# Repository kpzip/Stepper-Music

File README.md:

# Stepper-Music
Music with Stepper Motors!

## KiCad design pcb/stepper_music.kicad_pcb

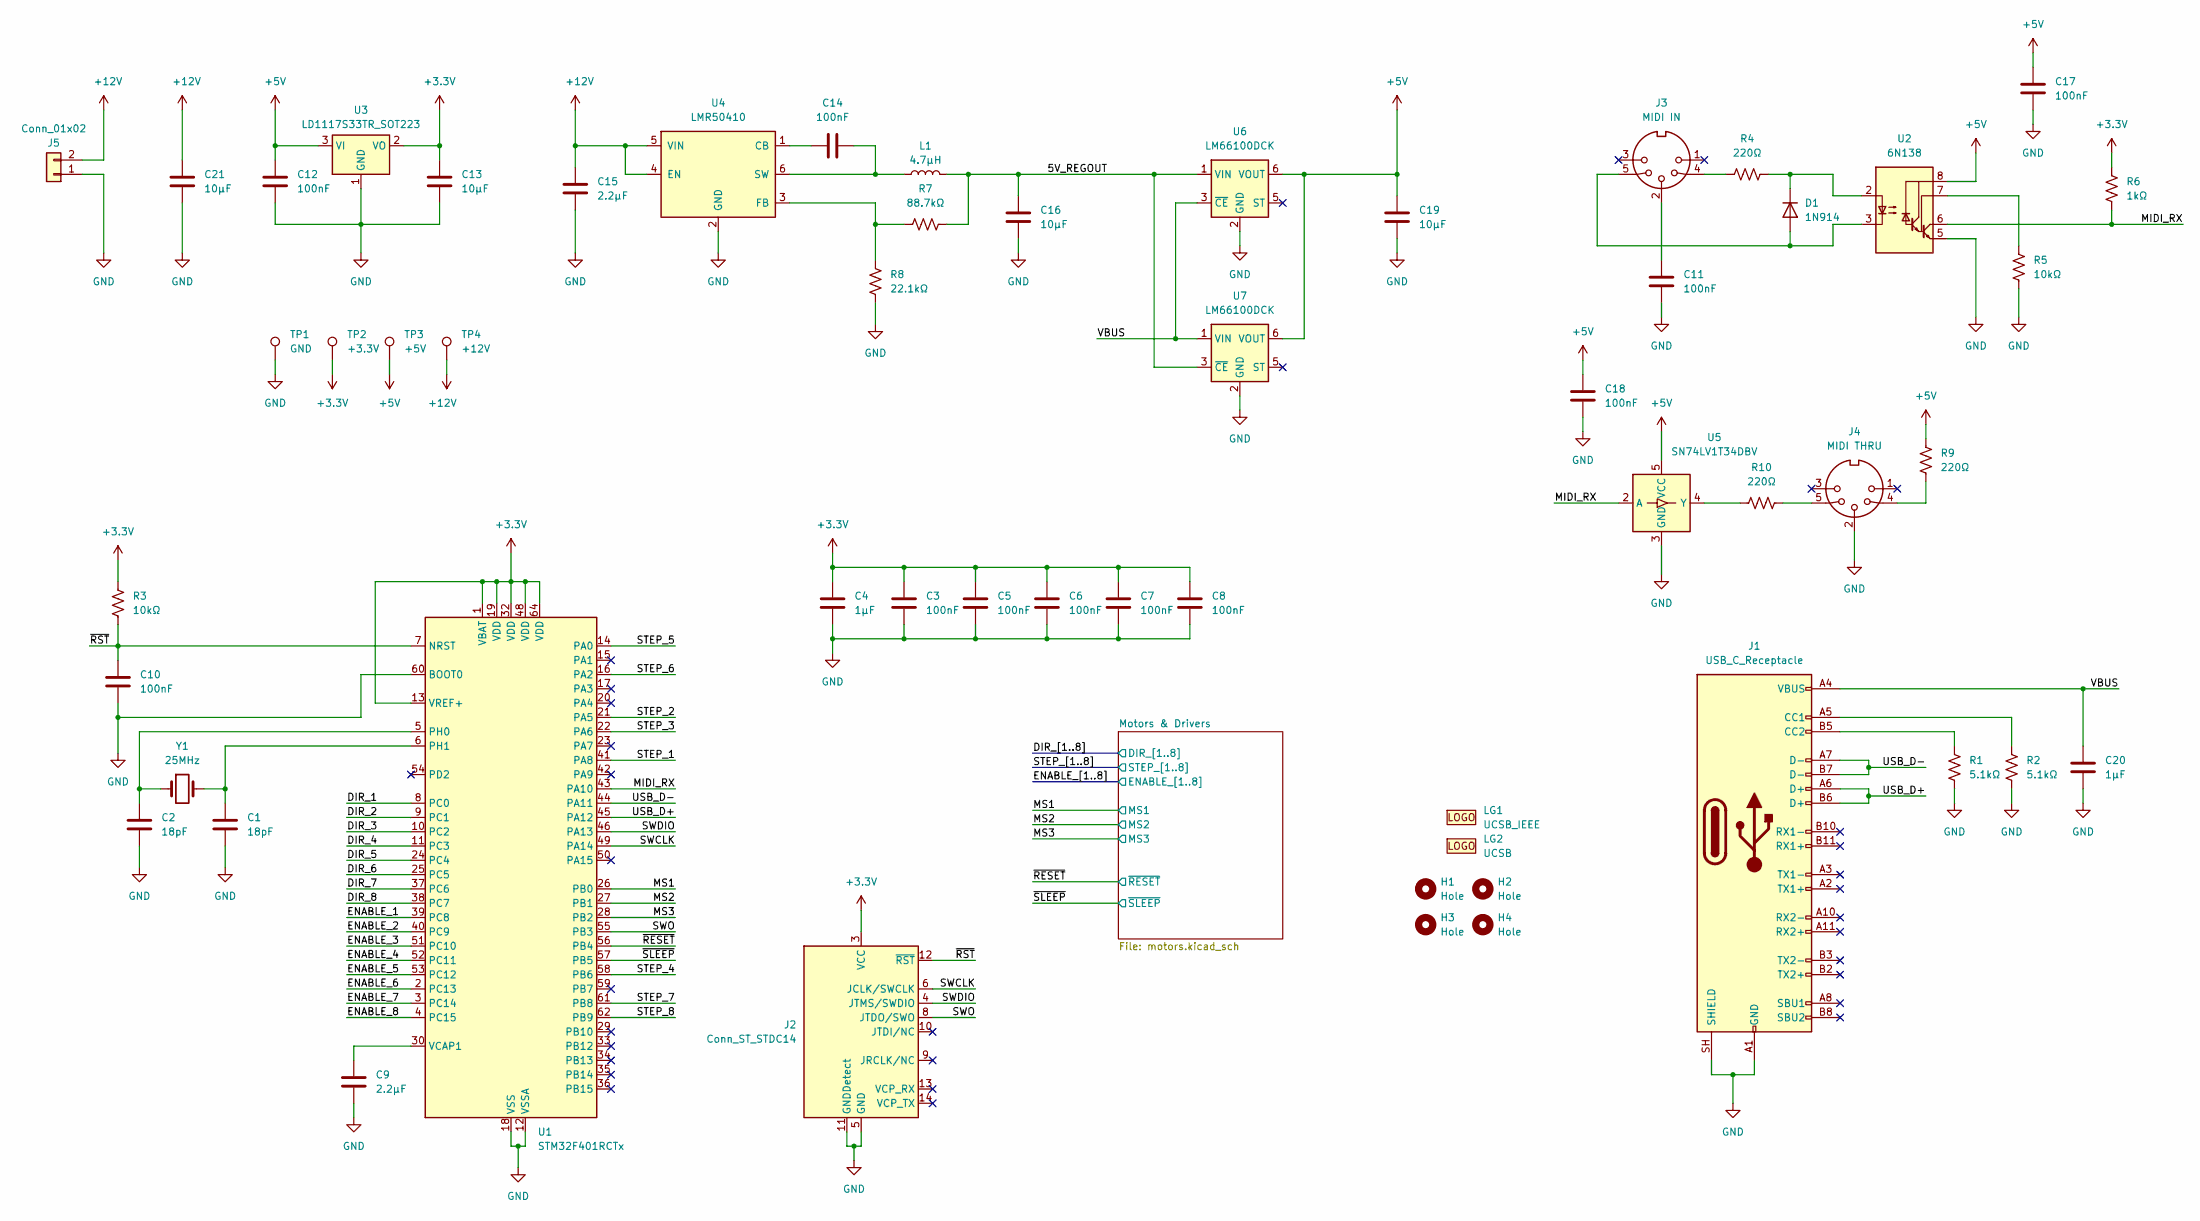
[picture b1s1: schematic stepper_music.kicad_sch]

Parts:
C1, C2: 18pF; C_0402_1005Metric; Manufacturer Part Number GJM1555C1H180GB01D
C3, C5, C6, C7, C8, C10, C11, C12, C14, C17, C18: 100nF; C_1206_3216Metric_Pad1.33x1.80mm_HandSolder; Manufacturer Part Number 1206B104K500CT
C4, C20: 1μF; C_1206_3216Metric_Pad1.33x1.80mm_HandSolder; Manufacturer Part Number CL31B105KAHNNNE
C9, C15: 2.2μF; C_1206_3216Metric_Pad1.33x1.80mm_HandSolder; Manufacturer Part Number UMK316BJ225KD-T
C13, C16, C19, C21: 10μF; C_1206_3216Metric_Pad1.33x1.80mm_HandSolder; Manufacturer Part Number 1276-1181-1-ND
D1: 1N914; D_SOD-523; Manufacturer Part Number 1N914BWT
H1, H2, H3, H4: Hole; MountingHole_3.2mm_M3_DIN965
J1: USB_C_Receptacle; USB_C_Receptacle_short; Manufacturer Part Number USB4056-03-A
J2: Conn_ST_STDC14; PinHeader_2x07_P1.27mm_Vertical_SMD; Manufacturer Part Number FTSH-107-01-L-DV-K
J3: MIDI IN; KYCON_KCDX-5S-N; Manufacturer Part Number KCDX-5S-N
J4: MIDI THRU; KYCON_KCDX-5S-N; Manufacturer Part Number KCDX-5S-N
J5: Conn_01x02; AMASS_XT30PW-M_1x02_P2.50mm_Horizontal; Manufacturer Part Number XT30PW-M30
L1: 4.7μH; L_1008_2520Metric_Pad1.43x2.20mm_HandSolder; Manufacturer Part Number DFE252012P-4R7M=P2
LG1: UCSB_IEEE; UCSB_IEEE_Logo
LG2: UCSB; UCSB_Medium
R1, R2: 5.1kΩ; R_1206_3216Metric_Pad1.30x1.75mm_HandSolder; Manufacturer Part Number RC1206FR-075K1L
R3, R5: 10kΩ; R_1206_3216Metric_Pad1.30x1.75mm_HandSolder; Manufacturer Part Number RMCF1206FT10K0
R4, R9, R10: 220Ω; R_1206_3216Metric_Pad1.30x1.75mm_HandSolder; Manufacturer Part Number RMCF1206FT220R
R6: 1kΩ; R_1206_3216Metric_Pad1.30x1.75mm_HandSolder; Manufacturer Part Number RC1206FR-071KL
R7: 88.7kΩ; R_1206_3216Metric_Pad1.30x1.75mm_HandSolder; Manufacturer Part Number RC1206FR-0788K7L
R8: 22.1kΩ; R_1206_3216Metric_Pad1.30x1.75mm_HandSolder; Manufacturer Part Number CRCW120622K1FKEAC
TP1: GND; TestPoint_Pad_D1.5mm
TP2: +3.3V; TestPoint_Pad_D1.5mm
TP3: +5V; TestPoint_Pad_D1.5mm
TP4: +12V; TestPoint_Pad_D1.5mm
U1: STM32F401RCTx; LQFP-64_10x10mm_P0.5mm; Manufacturer Part Number STM32F401RCT6
U2: 6N138; SOIC-8_3.9x4.9mm_P1.27mm; Manufacturer Part Number HCPL-0701
U3: LD1117S33TR_SOT223; SOT-223-3_TabPin2; Manufacturer Part Number LD1117S33TR
U4: LMR50410; SOT-23-6; Manufacturer Part Number 296-LMR50410Y5FQDBVRQ1CT-ND
U5: SN74LV1T34DBV; SOT-23-5; Manufacturer Part Number SN74LV1T34DBVR
U6, U7: LM66100DCK; SOT-363_SC-70-6; Manufacturer Part Number LM66100DCKR
Y1: 25MHz; Crystal_SMD_HC49-SD; Manufacturer Part Number ECS-250-18-5PX-F-TR

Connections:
+3.3V: C3.1, C4.1, C5.1, C6.1, C7.1, C8.1, C13.1, J2.3 (VCC), R3.1, R6.1, TP2.1 (1_1), U1.1 (VBAT), U1.13 (VREF+), U1.19 (VDD), U1.32 (VDD), U1.48 (VDD), U1.64 (VDD), U3.2 (VO); also elsewhere on the board
+5V: C12.1, C17.1, C18.1, C19.1, R9.2, TP3.1 (1_1), U2.8 (VCC), U3.3 (VI), U5.5 (VCC), U6.6 (VOUT), U7.6 (VOUT)
+12V: C15.1, C21.1, J5.2, TP4.1 (1_1), U4.4 (EN), U4.5 (VIN); also elsewhere on the board
/5V_REGOUT: C16.1, L1.2, R7.2, U6.1 (VIN), U7.3 (~CE)
/DIR_1: U1.8 (PC0); also elsewhere on the board
/DIR_2: U1.9 (PC1); also elsewhere on the board
/DIR_3: U1.10 (PC2); also elsewhere on the board
/DIR_4: U1.11 (PC3); also elsewhere on the board
/DIR_5: U1.24 (PC4); also elsewhere on the board
/DIR_6: U1.25 (PC5); also elsewhere on the board
/DIR_7: U1.37 (PC6); also elsewhere on the board
/DIR_8: U1.38 (PC7); also elsewhere on the board
/ENABLE_1: U1.39 (PC8); also elsewhere on the board
/ENABLE_2: U1.40 (PC9); also elsewhere on the board
/ENABLE_3: U1.51 (PC10); also elsewhere on the board
/ENABLE_4: U1.52 (PC11); also elsewhere on the board
/ENABLE_5: U1.53 (PC12); also elsewhere on the board
/ENABLE_6: U1.2 (PC13); also elsewhere on the board
/ENABLE_7: U1.3 (PC14); also elsewhere on the board
/ENABLE_8: U1.4 (PC15); also elsewhere on the board
/MIDI_RX: R6.2, U1.43 (PA10), U2.6 (VO2), U5.2 (A)
/MS1: U1.26 (PB0); also elsewhere on the board
/MS2: U1.27 (PB1); also elsewhere on the board
/MS3: U1.28 (PB2); also elsewhere on the board
/STEP_1: U1.41 (PA8); also elsewhere on the board
/STEP_2: U1.21 (PA5); also elsewhere on the board
/STEP_3: U1.22 (PA6); also elsewhere on the board
/STEP_4: U1.58 (PB6); also elsewhere on the board
/STEP_5: U1.14 (PA0); also elsewhere on the board
/STEP_6: U1.16 (PA2); also elsewhere on the board
/STEP_7: U1.61 (PB8); also elsewhere on the board
/STEP_8: U1.62 (PB9); also elsewhere on the board
/SWCLK: J2.6 (JCLK/SWCLK), U1.49 (PA14)
/SWDIO: J2.4 (JTMS/SWDIO), U1.46 (PA13)
/SWO: J2.8 (JTDO/SWO), U1.55 (PB3)
/USB_D+: J1.A6 (D+), J1.B6 (D+), U1.45 (PA12)
/USB_D-: J1.A7 (D-), J1.B7 (D-), U1.44 (PA11)
/VBUS: C20.1, J1.A4 (VBUS), J1.A9 (VBUS), J1.B4 (VBUS), J1.B9 (VBUS), U6.3 (~CE), U7.1 (VIN)
/~RESET: U1.56 (PB4); also elsewhere on the board
/~RST: C10.1, J2.12 (~RST), R3.2, U1.7 (NRST)
/~SLEEP: U1.57 (PB5); also elsewhere on the board
GND: C1.2, C2.2, C3.2, C4.2, C5.2, C6.2, C7.2, C8.2, C9.2, C10.2, C11.2, C12.2, C13.2, C15.2, C16.2, C17.2, C18.2, C19.2, C20.2, C21.2, J1.A1 (GND), J1.A12 (GND), J1.B1 (GND), J1.B12 (GND), J1.SH (SHIELD), J2.5 (GND), J2.7 (GND), J2.11 (GNDDetect), J4.2, J5.1, R1.2, R2.2, R5.2, R8.2, TP1.1 (1_1), U1.12 (VSSA), U1.18 (VSS), U1.31 (VSS), U1.47 (VSS), U1.60 (BOOT0), U1.63 (VSS), U2.5 (GND), U3.1 (GND), U4.2 (GND), U5.3 (GND), U6.2 (GND), U7.2 (GND); also elsewhere on the board
unnamed: C11.1, J3.2
unnamed: D1.2 (A), J3.5, U2.3 (C2)
unnamed: D1.1 (K), R4.2, U2.2 (C1)
unnamed: J1.A5 (CC1), R2.1
unnamed: J1.B5 (CC2), R1.1
unnamed: J3.4, R4.1
unnamed: J4.4, R9.1
unnamed: J4.5, R10.1
unnamed: C2.1, U1.5 (PH0), Y1.1
unnamed: C1.1, U1.6 (PH1), Y1.2
unnamed: C9.1, U1.30 (VCAP1)
unnamed: R5.1, U2.7 (VO1)
unnamed: C14.1, U4.1 (CB)
unnamed: R7.1, R8.1, U4.3 (FB)
unnamed: C14.2, L1.1, U4.6 (SW)
unnamed: R10.2, U5.4 (Y)

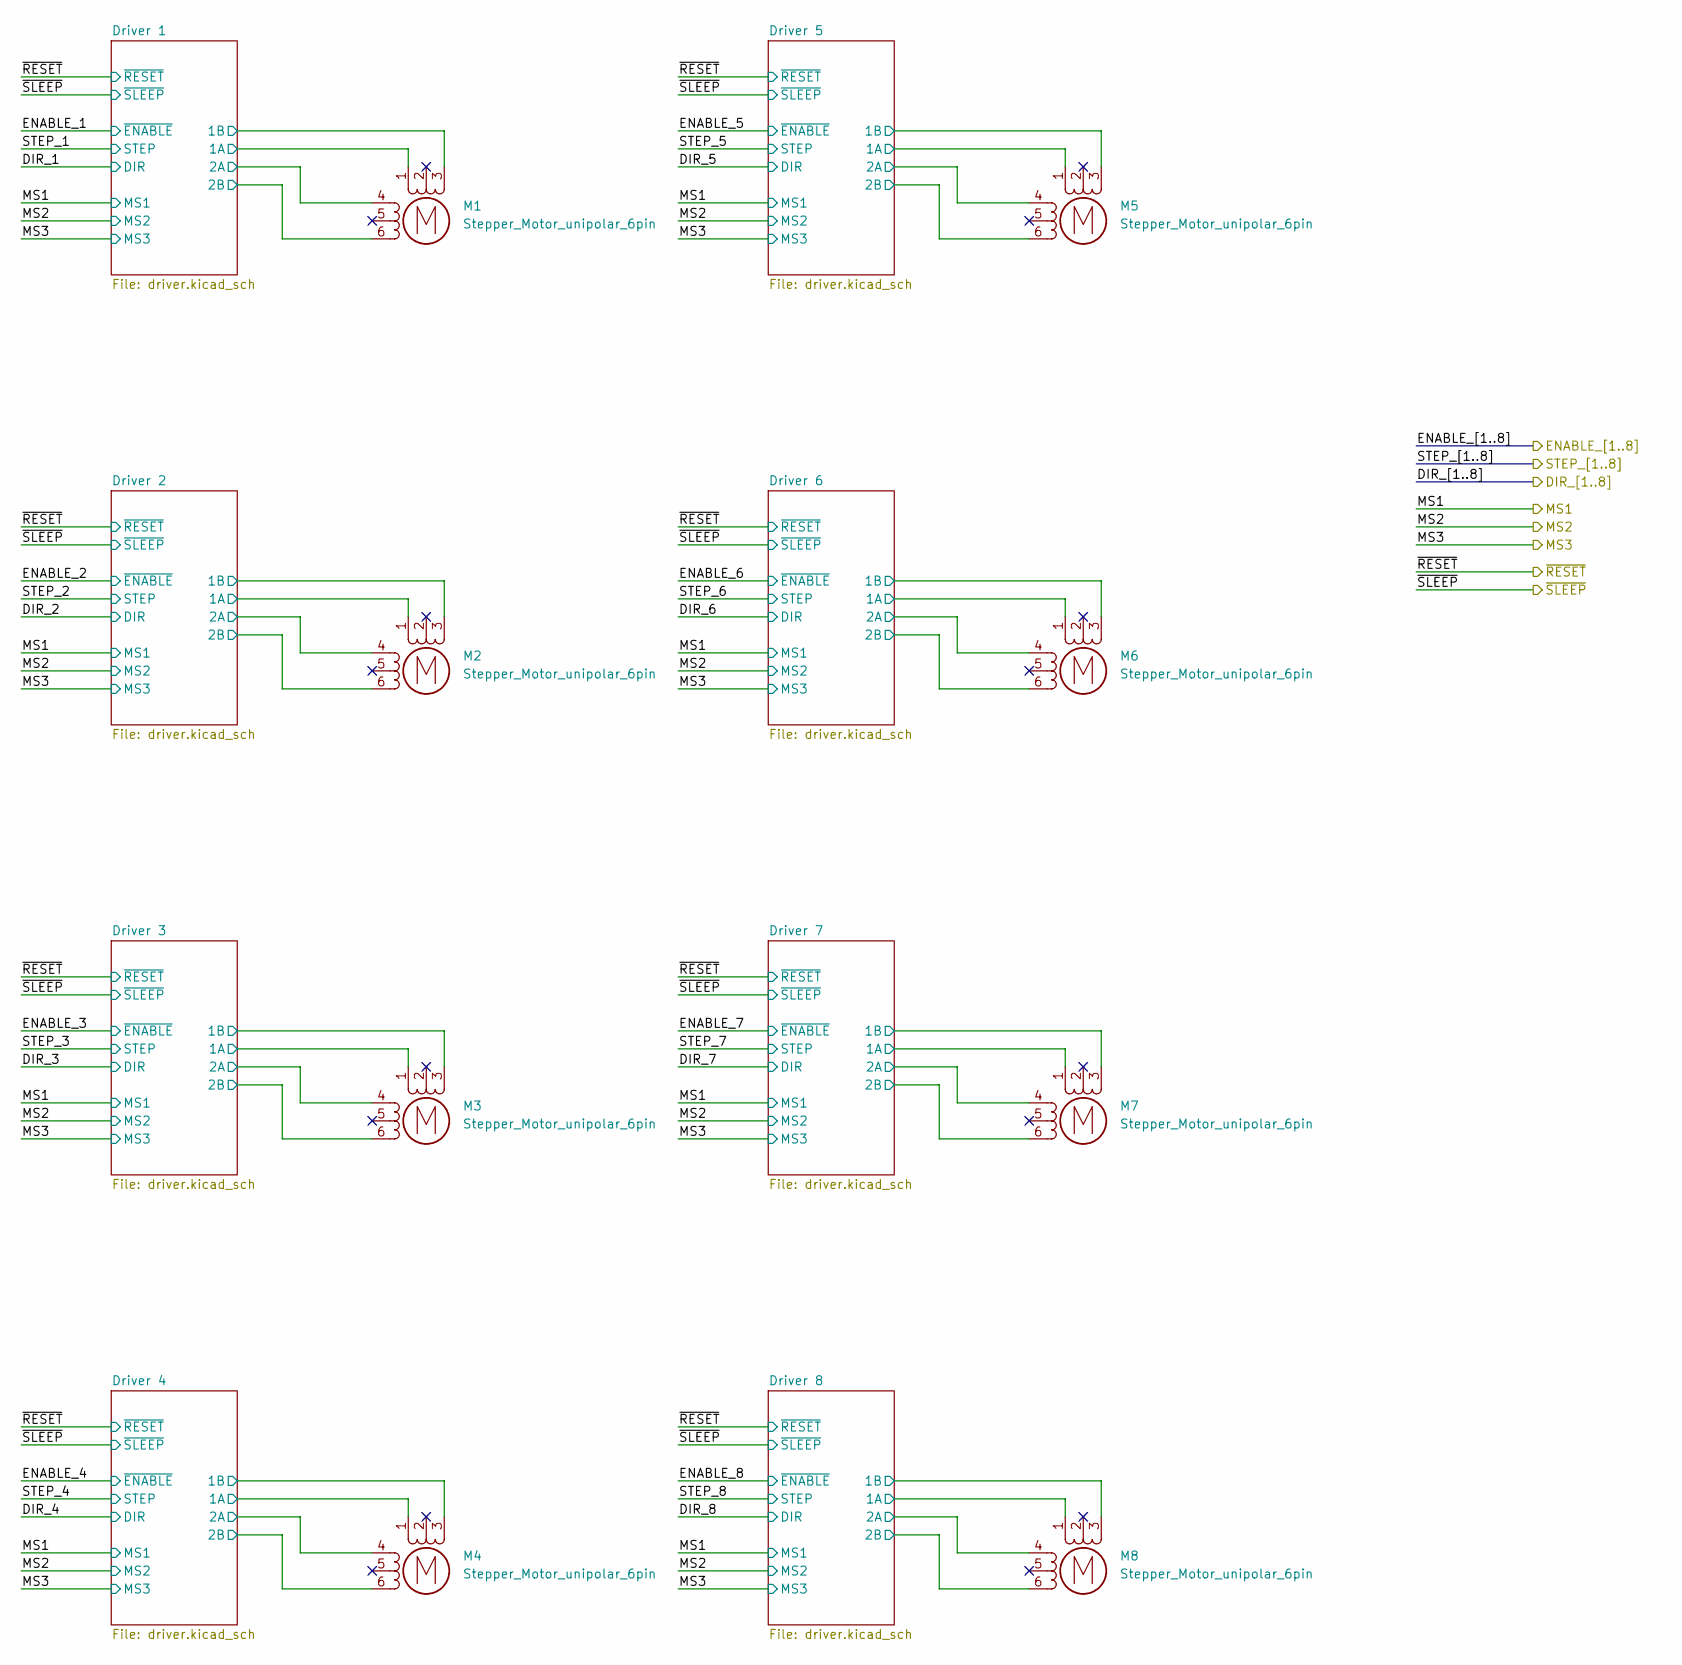
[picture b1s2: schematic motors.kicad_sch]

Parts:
M1, M2, M3, M4, M5, M6, M7, M8: Stepper_Motor_unipolar_6pin; JST_PH_B6B-PH-K_1x06_P2.00mm_Vertical; Manufacturer Part Number B6B-PH-K-S

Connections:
/Motors & Drivers/Driver 1/1A: M1.1; also elsewhere on the board
/Motors & Drivers/Driver 1/1B: M1.3 (-_3); also elsewhere on the board
/Motors & Drivers/Driver 1/2A: M1.4; also elsewhere on the board
/Motors & Drivers/Driver 1/2B: M1.6; also elsewhere on the board
/Motors & Drivers/Driver 2/1A: M2.1; also elsewhere on the board
/Motors & Drivers/Driver 2/1B: M2.3 (-_3); also elsewhere on the board
/Motors & Drivers/Driver 2/2A: M2.4; also elsewhere on the board
/Motors & Drivers/Driver 2/2B: M2.6; also elsewhere on the board
/Motors & Drivers/Driver 3/1A: M3.1; also elsewhere on the board
/Motors & Drivers/Driver 3/1B: M3.3 (-_3); also elsewhere on the board
/Motors & Drivers/Driver 3/2A: M3.4; also elsewhere on the board
/Motors & Drivers/Driver 3/2B: M3.6; also elsewhere on the board
/Motors & Drivers/Driver 4/1A: M4.1; also elsewhere on the board
/Motors & Drivers/Driver 4/1B: M4.3 (-_3); also elsewhere on the board
/Motors & Drivers/Driver 4/2A: M4.4; also elsewhere on the board
/Motors & Drivers/Driver 4/2B: M4.6; also elsewhere on the board
/Motors & Drivers/Driver 5/1A: M5.1; also elsewhere on the board
/Motors & Drivers/Driver 5/1B: M5.3 (-_3); also elsewhere on the board
/Motors & Drivers/Driver 5/2A: M5.4; also elsewhere on the board
/Motors & Drivers/Driver 5/2B: M5.6; also elsewhere on the board
/Motors & Drivers/Driver 6/1A: M6.1; also elsewhere on the board
/Motors & Drivers/Driver 6/1B: M6.3 (-_3); also elsewhere on the board
/Motors & Drivers/Driver 6/2A: M6.4; also elsewhere on the board
/Motors & Drivers/Driver 6/2B: M6.6; also elsewhere on the board
/Motors & Drivers/Driver 7/1A: M7.1; also elsewhere on the board
/Motors & Drivers/Driver 7/1B: M7.3 (-_3); also elsewhere on the board
/Motors & Drivers/Driver 7/2A: M7.4; also elsewhere on the board
/Motors & Drivers/Driver 7/2B: M7.6; also elsewhere on the board
/Motors & Drivers/Driver 8/1A: M8.1; also elsewhere on the board
/Motors & Drivers/Driver 8/1B: M8.3 (-_3); also elsewhere on the board
/Motors & Drivers/Driver 8/2A: M8.4; also elsewhere on the board
/Motors & Drivers/Driver 8/2B: M8.6; also elsewhere on the board

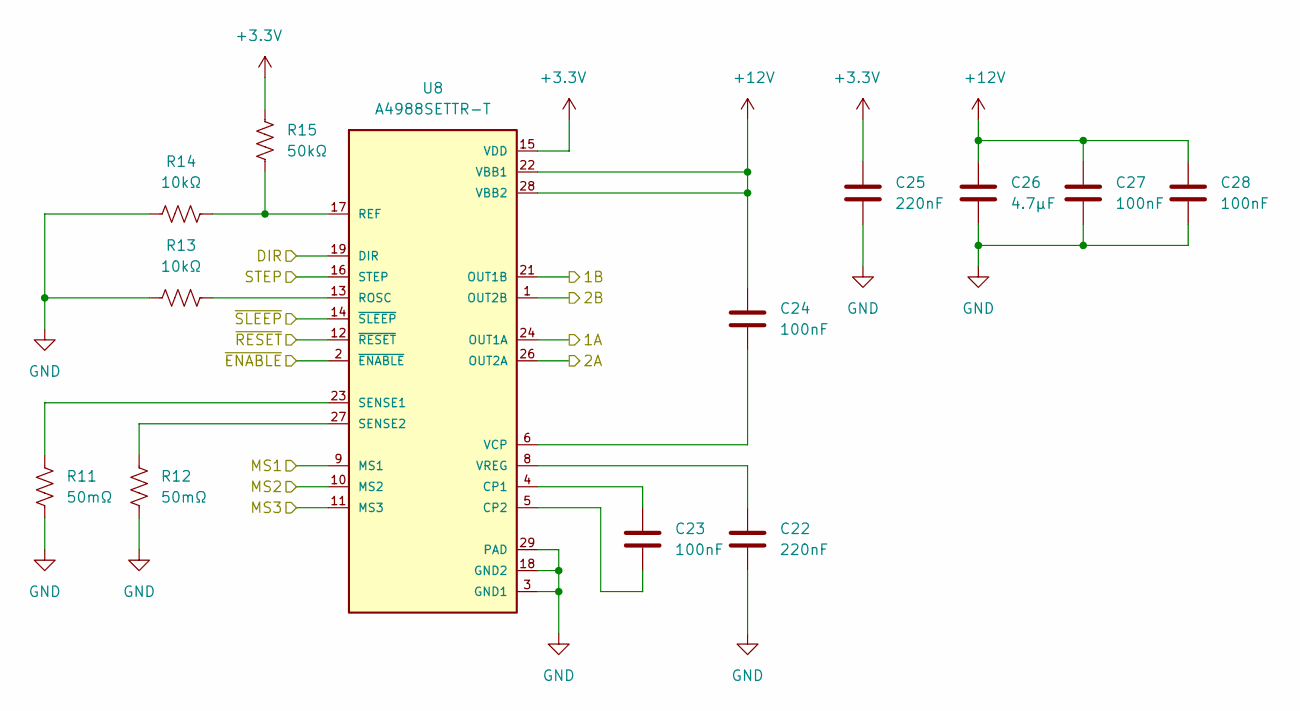
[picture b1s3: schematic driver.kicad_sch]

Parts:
C22, C25: 220nF; C_1206_3216Metric_Pad1.33x1.80mm_HandSolder; Manufacturer Part Number C1206C224K5RACTU
C23, C24, C27, C28: 100nF; C_1206_3216Metric_Pad1.33x1.80mm_HandSolder; Manufacturer Part Number 1206B104K500CT
C26: 4.7μF; C_1206_3216Metric_Pad1.33x1.80mm_HandSolder; Manufacturer Part Number CL31B475KAHNNNE
R11, R12: 50mΩ; R_1206_3216Metric_Pad1.30x1.75mm_HandSolder; Manufacturer Part Number CSR1206FT50L0
R13, R14: 10kΩ; R_1206_3216Metric_Pad1.30x1.75mm_HandSolder; Manufacturer Part Number RMCF1206FT10K0
R15: 50kΩ; R_1206_3216Metric_Pad1.30x1.75mm_HandSolder; Manufacturer Part Number RT1206BRD0750KL
U8: A4988SETTR-T; VQFN-28-1EP_5x5mm_P0.5mm_EP3.25x3.25mm_ThermalVias; Manufacturer Part Number A4988SETTR-T

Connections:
+3.3V: C25.1, R15.2, U8.15 (VDD); also elsewhere on the board
+12V: C24.1, C26.1, C27.1, C28.1, U8.22 (VBB1), U8.28 (VBB2); also elsewhere on the board
/DIR_1: U8.19 (DIR); also elsewhere on the board
/ENABLE_1: U8.2 (~ENABLE); also elsewhere on the board
/MS1: U8.9 (MS1); also elsewhere on the board
/MS2: U8.10 (MS2); also elsewhere on the board
/MS3: U8.11 (MS3); also elsewhere on the board
/Motors & Drivers/Driver 1/1A: U8.24 (OUT1A); also elsewhere on the board
/Motors & Drivers/Driver 1/1B: U8.21 (OUT1B); also elsewhere on the board
/Motors & Drivers/Driver 1/2A: U8.26 (OUT2A); also elsewhere on the board
/Motors & Drivers/Driver 1/2B: U8.1 (OUT2B); also elsewhere on the board
/STEP_1: U8.16 (STEP); also elsewhere on the board
/~RESET: U8.12 (~RESET); also elsewhere on the board
/~SLEEP: U8.14 (~SLEEP); also elsewhere on the board
GND: C22.2, C25.2, C26.2, C27.2, C28.2, R11.2, R12.2, R13.1, R14.1, U8.3 (GND1), U8.18 (GND2), U8.29 (PAD); also elsewhere on the board
unnamed: C23.1, U8.4 (CP1)
unnamed: C23.2, U8.5 (CP2)
unnamed: R14.2, R15.1, U8.17 (REF)
unnamed: R13.2, U8.13 (ROSC)
unnamed: R11.1, U8.23 (SENSE1)
unnamed: R12.1, U8.27 (SENSE2)
unnamed: C24.2, U8.6 (VCP)
unnamed: C22.1, U8.8 (VREG)

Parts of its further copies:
C29, C30, C34, C35, C36, C37, C41, C42, C43, C44, C48, C49, C50, C51, C55, C56, C57, C58, C62, C63, C64, C65, C69, C70, C71, C72, C76, C77: 100nF; C_1206_3216Metric_Pad1.33x1.80mm_HandSolder; Manufacturer Part Number 1206B104K500CT
C31, C32, C38, C39, C45, C46, C52, C53, C59, C60, C66, C67, C73, C74: 220nF; C_1206_3216Metric_Pad1.33x1.80mm_HandSolder; Manufacturer Part Number C1206C224K5RACTU
C33, C40, C47, C54, C61, C68, C75: 4.7μF; C_1206_3216Metric_Pad1.33x1.80mm_HandSolder; Manufacturer Part Number CL31B475KAHNNNE
R16, R17, R21, R22, R26, R27, R31, R32, R36, R37, R41, R42, R46, R47: 50mΩ; R_1206_3216Metric_Pad1.30x1.75mm_HandSolder; Manufacturer Part Number CSR1206FT50L0
R18, R19, R23, R24, R28, R29, R33, R34, R38, R39, R43, R44, R48, R49: 10kΩ; R_1206_3216Metric_Pad1.30x1.75mm_HandSolder; Manufacturer Part Number RMCF1206FT10K0
R20, R25, R30, R35, R40, R45, R50: 50kΩ; R_1206_3216Metric_Pad1.30x1.75mm_HandSolder; Manufacturer Part Number RT1206BRD0750KL
U9, U10, U11, U12, U13, U14, U15: A4988SETTR-T; VQFN-28-1EP_5x5mm_P0.5mm_EP3.25x3.25mm_ThermalVias; Manufacturer Part Number A4988SETTR-T

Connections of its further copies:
+3.3V: C32.1, C39.1, C46.1, C53.1, C60.1, C67.1, C74.1, R20.2, R25.2, R30.2, R35.2, R40.2, R45.2, R50.2, U9.15 (VDD), U10.15 (VDD), U11.15 (VDD), U12.15 (VDD), U13.15 (VDD), U14.15 (VDD), U15.15 (VDD); also elsewhere on the board
+12V: C30.1, C33.1, C34.1, C35.1, C37.1, C40.1, C41.1, C42.1, C44.1, C47.1, C48.1, C49.1, C51.1, C54.1, C55.1, C56.1, C58.1, C61.1, C62.1, C63.1, C65.1, C68.1, C69.1, C70.1, C72.1, C75.1, C76.1, C77.1, U9.22 (VBB1), U9.28 (VBB2), U10.22 (VBB1), U10.28 (VBB2), U11.22 (VBB1), U11.28 (VBB2), U12.22 (VBB1), U12.28 (VBB2), U13.22 (VBB1), U13.28 (VBB2), U14.22 (VBB1), U14.28 (VBB2), U15.22 (VBB1), U15.28 (VBB2); also elsewhere on the board
/DIR_2: U9.19 (DIR); also elsewhere on the board
/DIR_3: U10.19 (DIR); also elsewhere on the board
/DIR_4: U11.19 (DIR); also elsewhere on the board
/DIR_5: U12.19 (DIR); also elsewhere on the board
/DIR_6: U13.19 (DIR); also elsewhere on the board
/DIR_7: U14.19 (DIR); also elsewhere on the board
/DIR_8: U15.19 (DIR); also elsewhere on the board
/ENABLE_2: U9.2 (~ENABLE); also elsewhere on the board
/ENABLE_3: U10.2 (~ENABLE); also elsewhere on the board
/ENABLE_4: U11.2 (~ENABLE); also elsewhere on the board
/ENABLE_5: U12.2 (~ENABLE); also elsewhere on the board
/ENABLE_6: U13.2 (~ENABLE); also elsewhere on the board
/ENABLE_7: U14.2 (~ENABLE); also elsewhere on the board
/ENABLE_8: U15.2 (~ENABLE); also elsewhere on the board
/MS1: U9.9 (MS1), U10.9 (MS1), U11.9 (MS1), U12.9 (MS1), U13.9 (MS1), U14.9 (MS1), U15.9 (MS1); also elsewhere on the board
/MS2: U9.10 (MS2), U10.10 (MS2), U11.10 (MS2), U12.10 (MS2), U13.10 (MS2), U14.10 (MS2), U15.10 (MS2); also elsewhere on the board
/MS3: U9.11 (MS3), U10.11 (MS3), U11.11 (MS3), U12.11 (MS3), U13.11 (MS3), U14.11 (MS3), U15.11 (MS3); also elsewhere on the board
/Motors & Drivers/Driver 2/1A: U9.24 (OUT1A); also elsewhere on the board
/Motors & Drivers/Driver 2/1B: U9.21 (OUT1B); also elsewhere on the board
/Motors & Drivers/Driver 2/2A: U9.26 (OUT2A); also elsewhere on the board
/Motors & Drivers/Driver 2/2B: U9.1 (OUT2B); also elsewhere on the board
/Motors & Drivers/Driver 3/1A: U10.24 (OUT1A); also elsewhere on the board
/Motors & Drivers/Driver 3/1B: U10.21 (OUT1B); also elsewhere on the board
/Motors & Drivers/Driver 3/2A: U10.26 (OUT2A); also elsewhere on the board
/Motors & Drivers/Driver 3/2B: U10.1 (OUT2B); also elsewhere on the board
/Motors & Drivers/Driver 4/1A: U11.24 (OUT1A); also elsewhere on the board
/Motors & Drivers/Driver 4/1B: U11.21 (OUT1B); also elsewhere on the board
/Motors & Drivers/Driver 4/2A: U11.26 (OUT2A); also elsewhere on the board
/Motors & Drivers/Driver 4/2B: U11.1 (OUT2B); also elsewhere on the board
/Motors & Drivers/Driver 5/1A: U12.24 (OUT1A); also elsewhere on the board
/Motors & Drivers/Driver 5/1B: U12.21 (OUT1B); also elsewhere on the board
/Motors & Drivers/Driver 5/2A: U12.26 (OUT2A); also elsewhere on the board
/Motors & Drivers/Driver 5/2B: U12.1 (OUT2B); also elsewhere on the board
/Motors & Drivers/Driver 6/1A: U13.24 (OUT1A); also elsewhere on the board
/Motors & Drivers/Driver 6/1B: U13.21 (OUT1B); also elsewhere on the board
/Motors & Drivers/Driver 6/2A: U13.26 (OUT2A); also elsewhere on the board
/Motors & Drivers/Driver 6/2B: U13.1 (OUT2B); also elsewhere on the board
/Motors & Drivers/Driver 7/1A: U14.24 (OUT1A); also elsewhere on the board
/Motors & Drivers/Driver 7/1B: U14.21 (OUT1B); also elsewhere on the board
/Motors & Drivers/Driver 7/2A: U14.26 (OUT2A); also elsewhere on the board
/Motors & Drivers/Driver 7/2B: U14.1 (OUT2B); also elsewhere on the board
/Motors & Drivers/Driver 8/1A: U15.24 (OUT1A); also elsewhere on the board
/Motors & Drivers/Driver 8/1B: U15.21 (OUT1B); also elsewhere on the board
/Motors & Drivers/Driver 8/2A: U15.26 (OUT2A); also elsewhere on the board
/Motors & Drivers/Driver 8/2B: U15.1 (OUT2B); also elsewhere on the board
/STEP_2: U9.16 (STEP); also elsewhere on the board
/STEP_3: U10.16 (STEP); also elsewhere on the board
/STEP_4: U11.16 (STEP); also elsewhere on the board
/STEP_5: U12.16 (STEP); also elsewhere on the board
/STEP_6: U13.16 (STEP); also elsewhere on the board
/STEP_7: U14.16 (STEP); also elsewhere on the board
/STEP_8: U15.16 (STEP); also elsewhere on the board
/~RESET: U9.12 (~RESET), U10.12 (~RESET), U11.12 (~RESET), U12.12 (~RESET), U13.12 (~RESET), U14.12 (~RESET), U15.12 (~RESET); also elsewhere on the board
/~SLEEP: U9.14 (~SLEEP), U10.14 (~SLEEP), U11.14 (~SLEEP), U12.14 (~SLEEP), U13.14 (~SLEEP), U14.14 (~SLEEP), U15.14 (~SLEEP); also elsewhere on the board
GND: C31.2, C32.2, C33.2, C34.2, C35.2, C38.2, C39.2, C40.2, C41.2, C42.2, C45.2, C46.2, C47.2, C48.2, C49.2, C52.2, C53.2, C54.2, C55.2, C56.2, C59.2, C60.2, C61.2, C62.2, C63.2, C66.2, C67.2, C68.2, C69.2, C70.2, C73.2, C74.2, C75.2, C76.2, C77.2, R16.2, R17.2, R18.1, R19.1, R21.2, R22.2, R23.1, R24.1, R26.2, R27.2, R28.1, R29.1, R31.2, R32.2, R33.1, R34.1, R36.2, R37.2, R38.1, R39.1, R41.2, R42.2, R43.1, R44.1, R46.2, R47.2, R48.1, R49.1, U9.3 (GND1), U9.18 (GND2), U9.29 (PAD), U10.3 (GND1), U10.18 (GND2), U10.29 (PAD), U11.3 (GND1), U11.18 (GND2), U11.29 (PAD), U12.3 (GND1), U12.18 (GND2), U12.29 (PAD), U13.3 (GND1), U13.18 (GND2), U13.29 (PAD), U14.3 (GND1), U14.18 (GND2), U14.29 (PAD), U15.3 (GND1), U15.18 (GND2), U15.29 (PAD); also elsewhere on the board
unnamed: C29.1, U9.4 (CP1)
unnamed: C29.2, U9.5 (CP2)
unnamed: R18.2, R20.1, U9.17 (REF)
unnamed: R19.2, U9.13 (ROSC)
unnamed: R16.1, U9.23 (SENSE1)
unnamed: R17.1, U9.27 (SENSE2)
unnamed: C30.2, U9.6 (VCP)
unnamed: C31.1, U9.8 (VREG)
unnamed: C36.1, U10.4 (CP1)
unnamed: C36.2, U10.5 (CP2)
unnamed: R23.2, R25.1, U10.17 (REF)
unnamed: R24.2, U10.13 (ROSC)
unnamed: R21.1, U10.23 (SENSE1)
unnamed: R22.1, U10.27 (SENSE2)
unnamed: C37.2, U10.6 (VCP)
unnamed: C38.1, U10.8 (VREG)
unnamed: C43.1, U11.4 (CP1)
unnamed: C43.2, U11.5 (CP2)
unnamed: R28.2, R30.1, U11.17 (REF)
unnamed: R29.2, U11.13 (ROSC)
unnamed: R26.1, U11.23 (SENSE1)
unnamed: R27.1, U11.27 (SENSE2)
unnamed: C44.2, U11.6 (VCP)
unnamed: C45.1, U11.8 (VREG)
unnamed: C50.1, U12.4 (CP1)
unnamed: C50.2, U12.5 (CP2)
unnamed: R33.2, R35.1, U12.17 (REF)
unnamed: R34.2, U12.13 (ROSC)
unnamed: R31.1, U12.23 (SENSE1)
unnamed: R32.1, U12.27 (SENSE2)
unnamed: C51.2, U12.6 (VCP)
unnamed: C52.1, U12.8 (VREG)
unnamed: C57.1, U13.4 (CP1)
unnamed: C57.2, U13.5 (CP2)
unnamed: R38.2, R40.1, U13.17 (REF)
unnamed: R39.2, U13.13 (ROSC)
unnamed: R36.1, U13.23 (SENSE1)
unnamed: R37.1, U13.27 (SENSE2)
unnamed: C58.2, U13.6 (VCP)
unnamed: C59.1, U13.8 (VREG)
unnamed: C64.1, U14.4 (CP1)
unnamed: C64.2, U14.5 (CP2)
unnamed: R43.2, R45.1, U14.17 (REF)
unnamed: R44.2, U14.13 (ROSC)
unnamed: R41.1, U14.23 (SENSE1)
unnamed: R42.1, U14.27 (SENSE2)
unnamed: C65.2, U14.6 (VCP)
unnamed: C66.1, U14.8 (VREG)
unnamed: C71.1, U15.4 (CP1)
unnamed: C71.2, U15.5 (CP2)
unnamed: R48.2, R50.1, U15.17 (REF)
unnamed: R49.2, U15.13 (ROSC)
unnamed: R46.1, U15.23 (SENSE1)
unnamed: R47.1, U15.27 (SENSE2)
unnamed: C72.2, U15.6 (VCP)
unnamed: C73.1, U15.8 (VREG)

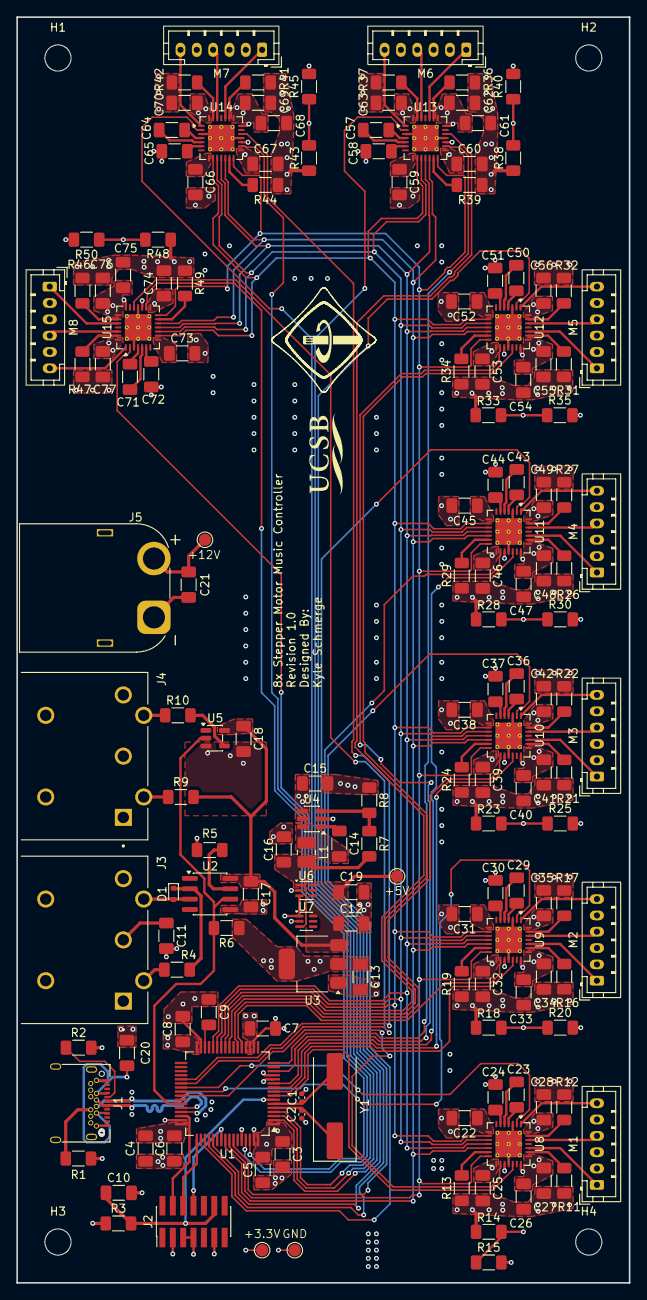
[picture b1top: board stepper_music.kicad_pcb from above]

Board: 4 copper layers, 75.0 x 155.0 mm, 168 parts (0 on the bottom side), 154 nets.

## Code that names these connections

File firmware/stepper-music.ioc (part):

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Mcu.Name=STM32F401R(B-C)Tx
Mcu.Package=LQFP64
Mcu.UserName=STM32F401RCTx
PA0-WKUP.Signal=S_TIM5_CH1
PA10.Mode=Asynchronous
PA10.Signal=USART1_RX
PA11.Mode=Device_Only
PA11.Signal=USB_OTG_FS_DM
PA12.Mode=Device_Only
PA12.Signal=USB_OTG_FS_DP
PA2.Signal=S_TIM9_CH1
PA5.Signal=S_TIM2_CH1_ETR
PA6.Signal=S_TIM3_CH1
PA8.Signal=S_TIM1_CH1
PA9.Mode=Asynchronous
PA9.Signal=USART1_TX
PB0.GPIOParameters=GPIO_Label
PB0.GPIO_Label=MS1
PB0.Signal=GPIO_Output
PB1.GPIOParameters=GPIO_Label
PB1.GPIO_Label=MS2
PB1.Signal=GPIO_Output
PB2.GPIOParameters=GPIO_Label
PB2.GPIO_Label=MS3
PB2.Signal=GPIO_Output
PB4.GPIOParameters=PinState,GPIO_Label
PB4.GPIO_Label=RESET
PB4.PinState=GPIO_PIN_SET
PB4.Signal=GPIO_Output
PB5.GPIOParameters=PinState,GPIO_Label
PB5.GPIO_Label=SLEEP
PB5.PinState=GPIO_PIN_SET
PB5.Signal=GPIO_Output
PB6.Signal=S_TIM4_CH1
PB8.Signal=S_TIM10_CH1
PB9.Signal=S_TIM11_CH1
PC0.GPIOParameters=GPIO_Label
PC0.GPIO_Label=DIR_1
PC0.Signal=GPIO_Output
PC1.GPIOParameters=GPIO_Label
PC1.GPIO_Label=DIR_2
PC1.Signal=GPIO_Output
PC10.GPIOParameters=GPIO_Label
PC10.GPIO_Label=ENABLE_3
PC10.Signal=GPIO_Output
PC11.GPIOParameters=GPIO_Label
PC11.GPIO_Label=ENABLE_4
PC11.Signal=GPIO_Output
PC12.GPIOParameters=GPIO_Label
PC12.GPIO_Label=ENABLE_5
PC12.Signal=GPIO_Output
PC13-ANTI_TAMP.GPIOParameters=GPIO_Label
PC13-ANTI_TAMP.GPIO_Label=ENABLE_6
PC13-ANTI_TAMP.Signal=GPIO_Output
PC14-OSC32_IN.GPIOParameters=GPIO_Speed,GPIO_Label
PC14-OSC32_IN.GPIO_Label=ENABLE_7
PC14-OSC32_IN.GPIO_Speed=GPIO_SPEED_FREQ_LOW
PC14-OSC32_IN.Signal=GPIO_Output
PC15-OSC32_OUT.GPIOParameters=GPIO_Label
PC15-OSC32_OUT.GPIO_Label=ENABLE_8
PC15-OSC32_OUT.Signal=GPIO_Output
PC2.GPIOParameters=GPIO_Label
PC2.GPIO_Label=DIR_3
PC2.Signal=GPIO_Output
PC3.GPIOParameters=GPIO_Label
PC3.GPIO_Label=DIR_4
PC3.Signal=GPIO_Output
PC4.GPIOParameters=GPIO_Label
PC4.GPIO_Label=DIR_5
PC4.Signal=GPIO_Output
PC5.GPIOParameters=GPIO_Label
PC5.GPIO_Label=DIR_6
PC5.Signal=GPIO_Output
PC6.GPIOParameters=GPIO_Label
PC6.GPIO_Label=DIR_7
PC6.Signal=GPIO_Output
PC7.GPIOParameters=GPIO_Label
PC7.GPIO_Label=DIR_8
PC7.Signal=GPIO_Output
PC8.GPIOParameters=GPIO_Label
PC8.GPIO_Label=ENABLE_1
PC8.Signal=GPIO_Output
PC9.GPIOParameters=GPIO_Label
PC9.GPIO_Label=ENABLE_2
PC9.Signal=GPIO_Output
PH0\ -\ OSC_IN.Mode=HSE-External-Oscillator
PH0\ -\ OSC_IN.Signal=RCC_OSC_IN
PH1\ -\ OSC_OUT.Mode=HSE-External-Oscillator
PH1\ -\ OSC_OUT.Signal=RCC_OSC_OUT
RCC.HSE_VALUE=25000000
RCC.SYSCLKFreq_VALUE=60000000
RCC.SYSCLKSource=RCC_SYSCLKSOURCE_PLLCLK
board=custom

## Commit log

2026-03-26 firmware
2026-03-30 work
2026-03-31 route
2026-03-31 drivers
2026-04-01 finish?
2026-04-02 name
2026-04-04 models
2026-04-05 fix sizes
2026-04-06 holes
2026-04-19 test
2026-04-25 fixes
